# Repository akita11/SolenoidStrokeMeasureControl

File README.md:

# Solenoid Stroke Measure & Control

Measuring Solenoid Stroke, which corresponds to the inductance, by sensing current waveform at OFF->ON state,calculated from resistance's voltage at source of nMOSFET, amplified by non-inverting amplifier.

## How to Use

- connect this board to M5Stck Core2's PortA.
- connect the solenoid and the power for it to this board

### for SolenoidStrokelUnit:

Using [SolenoidStrokeUNIT](https://github.com/akita11/SolenoidStrokeUNIT), trained models are in Control_ESP32/src or Control_Python. Technical details are [paper1](https://arxiv.org/abs/2405.11721) and [paper2](https://arxiv.org/abs/2411.07270)

- Measure_... for parameter measurement
- Control... for position control (using M5Stack or Python)

### for SolenoidMeasureControlUnit:

- generate PWM at PortA's pin3 (GPIO32). PWM frequency can be set for the solenoid used, such as 100Hz. 
- waveform on PortA's pin4 (GPIO33) gives current

## Measurement&Control Unit Board

available at [https://www.switch-science.com/products/10174].

(old: SolenoidMeasureControlUnit) available at [here](https://github.com/akita11/SolenoidStrokeMeasureControlUNIT) or [purchase here](https://www.switch-science.com/products/9717). 

## Experimental Results

(old: SolenoidMeasureControlUnit)

Test results are in 'test240424' folder. [Takaha's CBS07300580](https://www.takaha-japan.com/product/cbs0730/) with power suppply of 12V. R5=100k&R6=10k for x101 amplification, with R4, R7, R8, R9 unused.

## Author

Junichi Akita (akita@ifdl, @akita11)

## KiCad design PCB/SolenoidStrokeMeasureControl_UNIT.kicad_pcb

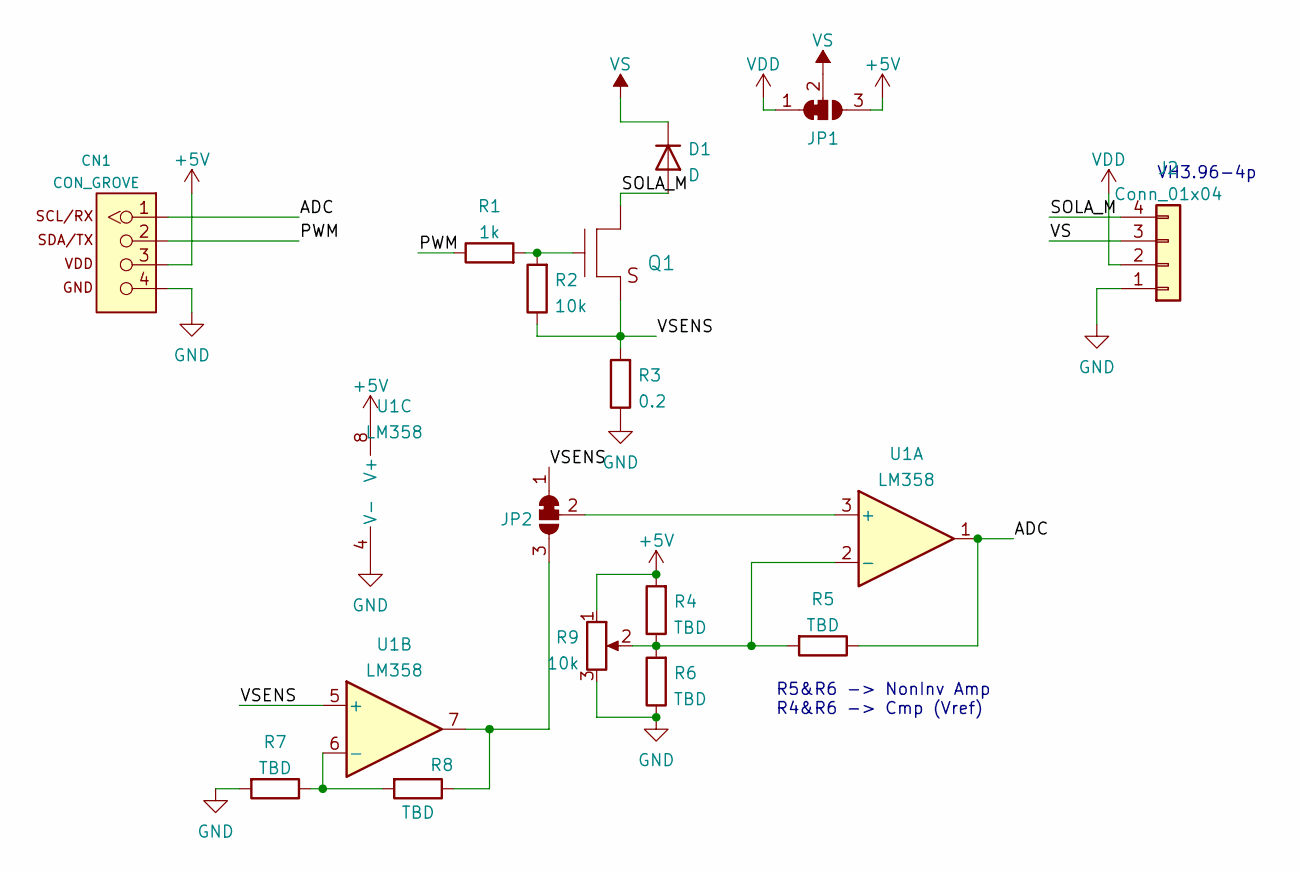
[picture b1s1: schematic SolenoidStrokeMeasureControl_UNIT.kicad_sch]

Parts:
CN1: CON_GROVE; CON_GROVE_H
D1: D; D_SOD-123F
J2: Conn_01x04; JST_VH_S4P-VH_1x04_P3.96mm_Horizontal
JP1, JP2: SolderJumper_3_Bridged12; SolderJumper-3_P1.3mm_Bridged2Bar12_Pad1.0x1.5mm
Q1: TR_NMOS_IRLML6344; SOT-23
R1: 1k; R_0603_1608Metric
R2: 10k; R_0603_1608Metric
R3: 0.2; R_1206_3216Metric
R4, R5, R6, R7, R8: TBD; R_0603_1608Metric
R9: 10k; Potentiometer_Bourns_3223W
U1: LM358; SO-8_5.3x6.2mm_P1.27mm

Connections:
+5V: CN1.3, JP1.3 (B), R4.2, R9.1, U1.8 (V+)
/ADC: CN1.1, R5.1, U1.1
/PWM: CN1.2, R1.1
/SOLA_M: D1.2 (A), J2.4, Q1.3 (D)
/VSENS: JP2.1 (A), Q1.2 (S), R2.1, R3.2, U1.5 (+)
GND: CN1.4, J2.1, R3.1, R6.1, R7.2, R9.3, U1.4 (V-)
unnamed: JP2.2 (C), U1.3 (+)
unnamed: JP2.3 (B), R8.1, U1.7
unnamed: Q1.1 (G), R1.2, R2.2
unnamed: R4.1, R5.2, R6.2, R9.2, U1.2 (-)
unnamed: R7.1, R8.2, U1.6 (-)
VDD: J2.2, JP1.1 (A)
VS: D1.1 (K), J2.3, JP1.2 (C)

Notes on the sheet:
R5&R6 -> NonInv Amp R4&R6 -> Cmp (Vref)
VH3.96-4p

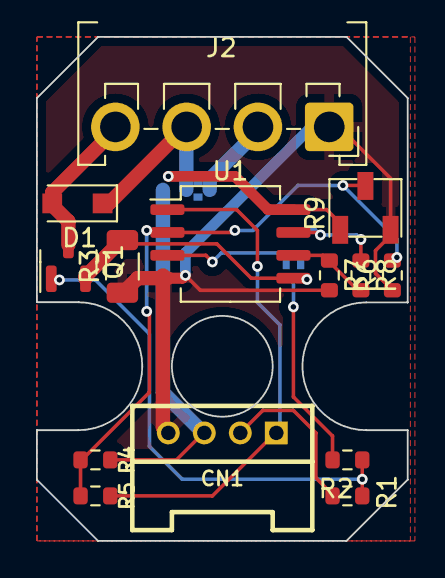
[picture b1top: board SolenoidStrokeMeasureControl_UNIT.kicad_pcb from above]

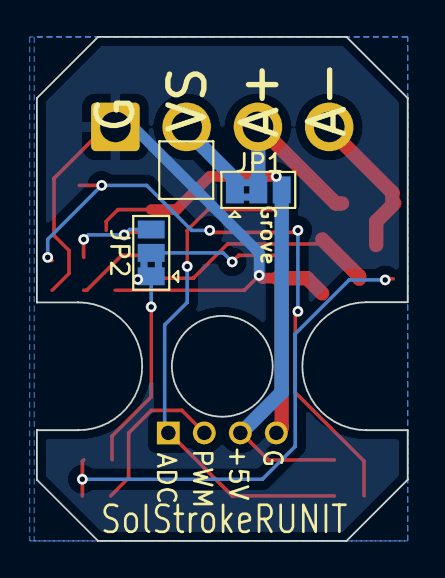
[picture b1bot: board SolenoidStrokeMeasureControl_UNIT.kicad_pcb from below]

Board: 2 copper layers, 20.6 x 28.0 mm, 16 parts (2 on the bottom side), 13 nets.

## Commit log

2024-04-25 add bom
2024-04-25 fix BOM typo
2024-05-02 add Measure_ArduinoUNO
2024-05-02 add ADC acquire
2024-05-08 add Arduino measure code
2024-05-09 add sim&calc, exp results
2024-05-09 add stroke-L measurement
2024-05-10 define LUT
2024-05-11 add interpolate for UNO
2024-05-11 fix typo
2024-05-13 add test for manual move
2024-05-13 function of pos calc
2024-05-13 preliminary position control
2024-05-13 tentative posision control
2024-05-14 P control
2024-05-14 PID control
2024-05-25 MCPWM test for ESP32 measure
2024-05-27 separate measure&control, ESP32
2024-05-27 position control
2024-05-27 update control, v0 update timing
2024-05-28 UNO measure
2024-05-29 ESP32 control (draft)
2024-05-29 trivial modifications
2024-05-29 MCPWM interrupt test
2024-05-31 Caliper measure,
2024-05-31 Mitsutoyo measure on UNO
2024-05-31 add header check for Mitsutoyo measure
2024-05-31 St by potentiometer
2024-06-03 GDS for position prediction
2024-06-09 update calcPos for LongStroke
2024-06-10 fader control for CBS0730, trial on estimating LongStroke
2024-06-10 improve prediction
2024-06-11 measure: mid diff, control: GDS
2024-06-11 Measure&Control for ESP32
2024-06-13 ESP32-CBS0730
2024-06-13 ESP32 control x2
2024-06-14 LongStroke position measure
2024-06-14 slider color for LongStroke+ESP32
2024-06-19 update readme, delete pcb
2024-07-01 position estimate by RandomForest
2024-07-01 pos prediction using RF & control
2024-07-02 draw PWM graph
2024-07-04 using NN
2024-07-04 add link to ChatGPT in NN
2024-07-04 test code for SDL2
2024-07-05 record for RF, tentative NN
2024-07-05 periodic PWM control & log for RF
2024-07-05 measure v0&v1 only, CoreS3
2024-07-08 working on NN
2024-07-10 MeasureESP32 Core2/S3 ifdef
2024-07-10 measure at 100&200Hz
2024-07-12 Ton up/down sweep, 5 times
2024-07-13 multiple measure average
2024-07-13 bug fix on Measure_ESP32
2024-07-13 NN TFLite
2024-07-14 tentative working NN
2024-07-14 control using NN (for test)
2024-07-14 add train.py
2024-07-14 CNN model for Pos&Temp
2024-07-15 position control usiing CNN
2024-07-16 add test
2024-07-17 Measure raw ADC
2024-07-17 controlNN based on precise measure
2024-07-17 NN control on PIO
2024-07-18 Fader for target position, no M5.update
2024-07-19 separated ESP32 measure&control
2024-07-19 USB-serial command
2024-07-19 control NN with MeasCtrl ATOM-S3
2024-07-19 edit .gitignore
2024-07-19 summarize folders
2024-07-19 summarize work
2024-07-19 add NN model
2024-07-19 NN control for CBS0730140
2024-07-19 model for CBS0730-140
2024-07-20 CNN models for 3 solenoids
2024-07-20 control temp measure
2024-07-20 add CH1284 model
2024-07-22 Meas&Ctrl for UNO
2024-07-22 Meas&Ctrl for Arduino
2024-07-23 controlNN pos_t by uart
2024-07-23 ControlNN start/stop
2024-07-24 ControlNN touch start/stop
2024-07-26 wait 2s for transient stable
2024-07-29 Nsample=10, long wait time for transition
2024-08-06 240806 measured model
2024-08-07 update test
2024-08-08 add TEST_ALL for ControlNN
2024-08-09 initial commit for ATtiny202 measure
2024-08-12 ATtiny202 skelton
2024-08-16 tentative setups for ATtiny202
2024-09-15 working UART&PWM
2024-09-15 config on f_cpu
2024-09-21 tentative TCA/EVSYS
2024-11-25 timerISR & UART command (partial)
2024-11-25 command implemented
2024-12-04 Meas&Ctrl ATtiny202
2024-12-05 averaging for ATtiny202
2024-12-15 SonMeasU+MeasureESP32
2024-12-25 working
2024-12-27 measure ESP32 for ATtiny UNIT
2025-01-25 add SSBH model for SolStrU
2025-01-26 control@200Hz using SolStrokeU
2025-03-04 update readme, add python code
